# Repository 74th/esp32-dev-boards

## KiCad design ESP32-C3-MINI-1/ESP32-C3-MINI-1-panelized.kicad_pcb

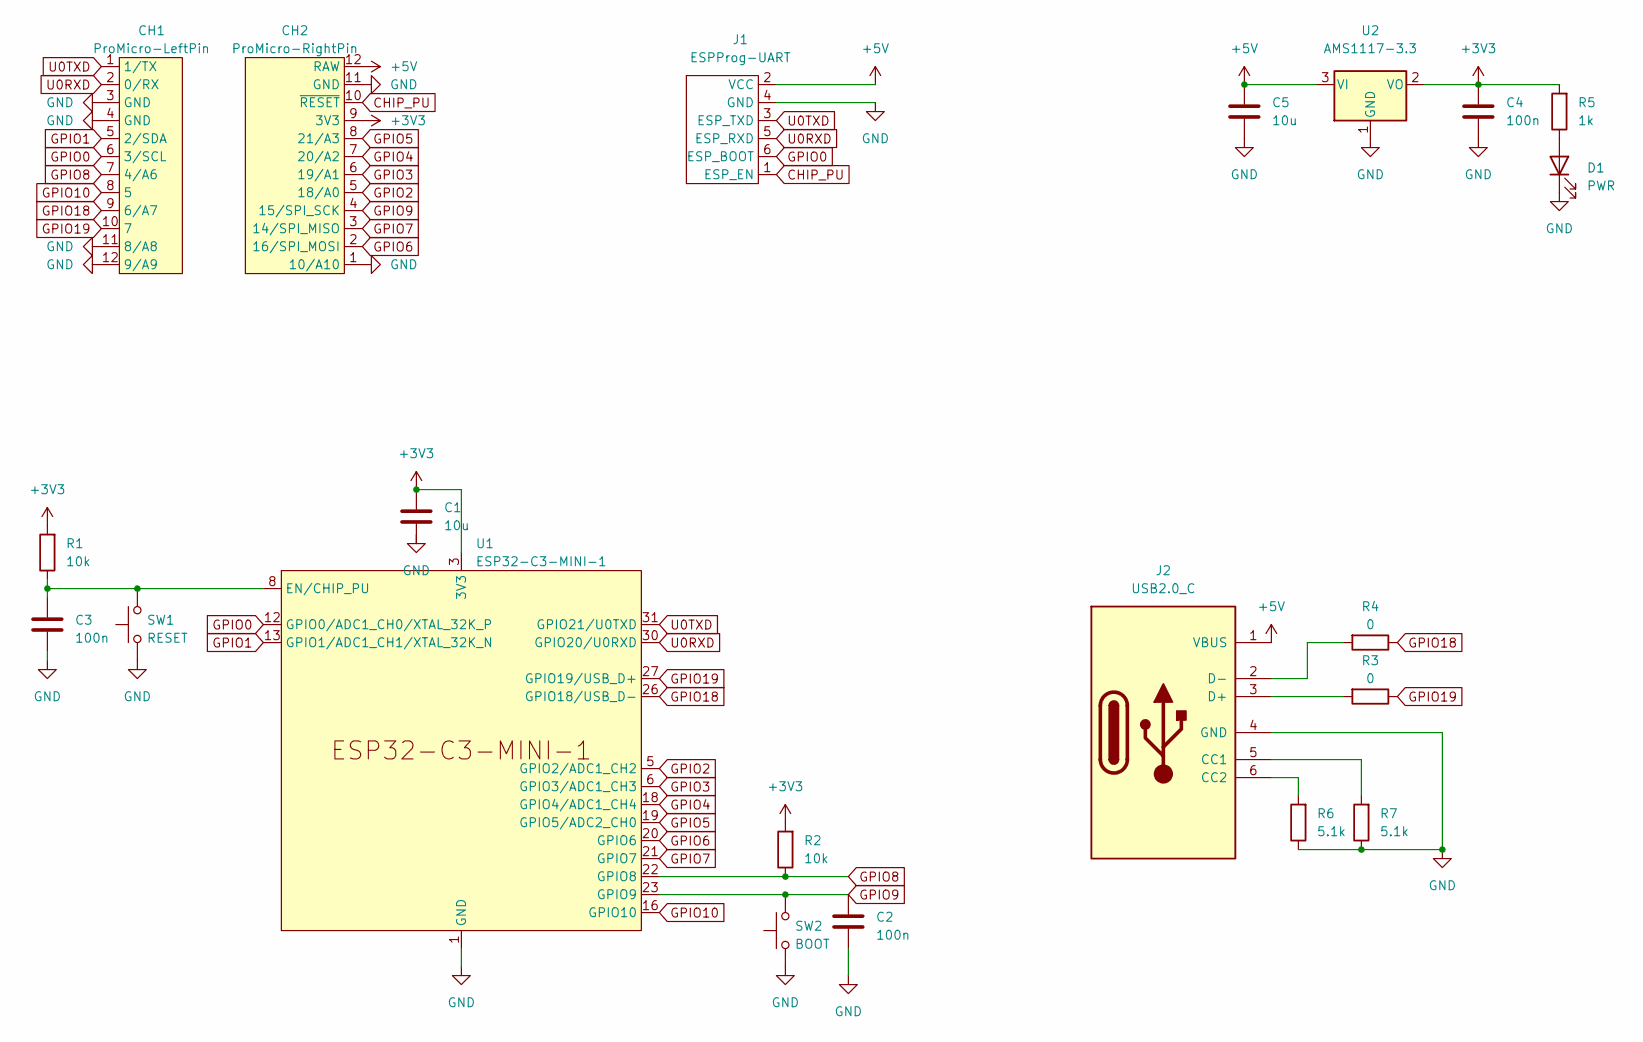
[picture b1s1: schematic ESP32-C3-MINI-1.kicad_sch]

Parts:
C1, C5: 10u; Capacitor_0805_2012
C2, C3, C4: 100n; Capacitor_0805_2012
CH1: ProMicro-LeftPin; ProMicro_LIKE_LEFT
CH2: ProMicro-RightPin; ProMicro_LIKE_RIGHT
D1: PWR; LED_0805_2012Metric_Pad1.15x1.40mm_HandSolder
J1: ESPProg-UART; BoxPinHeader_2x03_P1.27mm_Vertical
J2: USB2.0_C; USB-C-12-Pin-SMD
R1, R2: 10k; Register_0805_2012
R3, R4: 0; Register_0805_2012
R5: 1k; Register_0805_2012
R6, R7: 5.1k; Register_0805_2012
SW1: RESET; SKRPABE010
SW2: BOOT; SKRPABE010
U1: ESP32-C3-MINI-1
U2: AMS1117-3.3; Regulator_AMS1117_SOT-89

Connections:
+3V3: C1.1, C4.1, CH2.9 (3V3), R1.2, R2.2, R5.2, U1.3 (3V3), U2.2 (VO)
+5V: C5.1, CH2.12 (RAW), J1.2 (VCC), J2.1 (VBUS), U2.3 (VI)
CHIP_PU: CH2.10 (~RESET), J1.1 (ESP_EN)
GND: C2.2, C3.2, C4.2, C5.2, CH1.3 (GND), CH1.4 (GND), CH1.11 (8/A8), CH1.12 (9/A9), CH2.1 (10/A10), CH2.11 (GND), D1.1 (K), J1.4 (GND), J2.4 (GND), R6.1, R7.1, SW1.1, SW2.1, U1.1 (GND), U1.2 (GND), U1.11 (GND), U1.14 (GND), U1.36 (GND), U1.37 (GND), U1.38 (GND), U1.39 (GND), U1.40 (GND), U1.41 (GND), U1.42 (GND), U1.43 (GND), U1.44 (GND), U1.45 (GND), U1.46 (GND), U1.47 (GND), U1.48 (GND), U1.49 (GND), U1.50 (GND), U1.51 (GND), U1.52 (GND), U1.53 (GND), U2.1 (GND)
GPIO0: CH1.6 (3/SCL), J1.6 (ESP_BOOT), U1.12 (GPIO0/ADC1_CH0/XTAL_32K_P)
GPIO1: CH1.5 (2/SDA), U1.13 (GPIO1/ADC1_CH1/XTAL_32K_N)
GPIO2: CH2.5 (18/A0), U1.5 (GPIO2/ADC1_CH2)
GPIO3: CH2.6 (19/A1), U1.6 (GPIO3/ADC1_CH3)
GPIO4: CH2.7 (20/A2), U1.18 (GPIO4/ADC1_CH4)
GPIO5: CH2.8 (21/A3), U1.19 (GPIO5/ADC2_CH0)
GPIO6: CH2.2 (16/SPI_MOSI), U1.20 (GPIO6)
GPIO7: CH2.3 (14/SPI_MISO), U1.21 (GPIO7)
GPIO8: CH1.7 (4/A6), R2.1, U1.22 (GPIO8)
GPIO9: C2.1, CH2.4 (15/SPI_SCK), SW2.2, U1.23 (GPIO9)
GPIO10: CH1.8 (5), U1.16 (GPIO10)
GPIO18: CH1.9 (6/A7), R4.1, U1.26 (GPIO18/USB_D-)
GPIO19: CH1.10 (7), R3.1, U1.27 (GPIO19/USB_D+)
unnamed: D1.2 (A), R5.1
unnamed: J2.5 (CC1), R7.2
unnamed: J2.6 (CC2), R6.2
unnamed: J2.3 (D+), R3.2
unnamed: J2.2 (D-), R4.2
unnamed: C3.1, R1.1, SW1.2, U1.8 (EN/CHIP_PU)
U0RXD: CH1.2 (0/RX), J1.5 (ESP_RXD), U1.30 (GPIO20/U0RXD)
U0TXD: CH1.1 (1/TX), J1.3 (ESP_TXD), U1.31 (GPIO21/U0TXD)

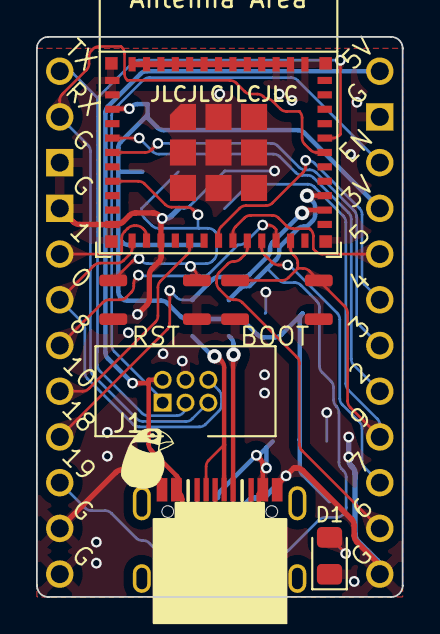
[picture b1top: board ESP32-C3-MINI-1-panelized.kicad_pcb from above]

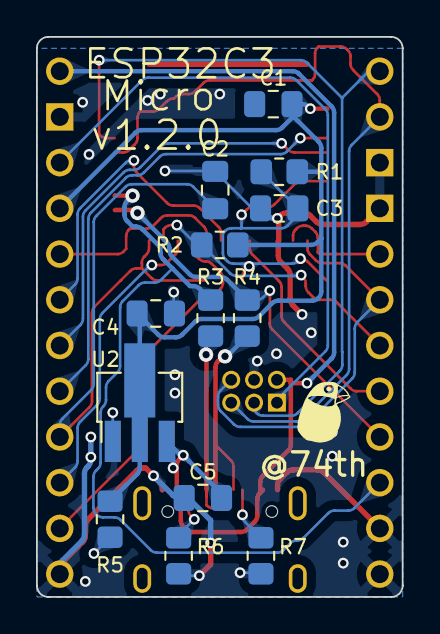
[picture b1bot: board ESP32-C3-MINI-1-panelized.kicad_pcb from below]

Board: 2 copper layers, 20.3 x 31.1 mm, 21 parts (13 on the bottom side), 25 nets.

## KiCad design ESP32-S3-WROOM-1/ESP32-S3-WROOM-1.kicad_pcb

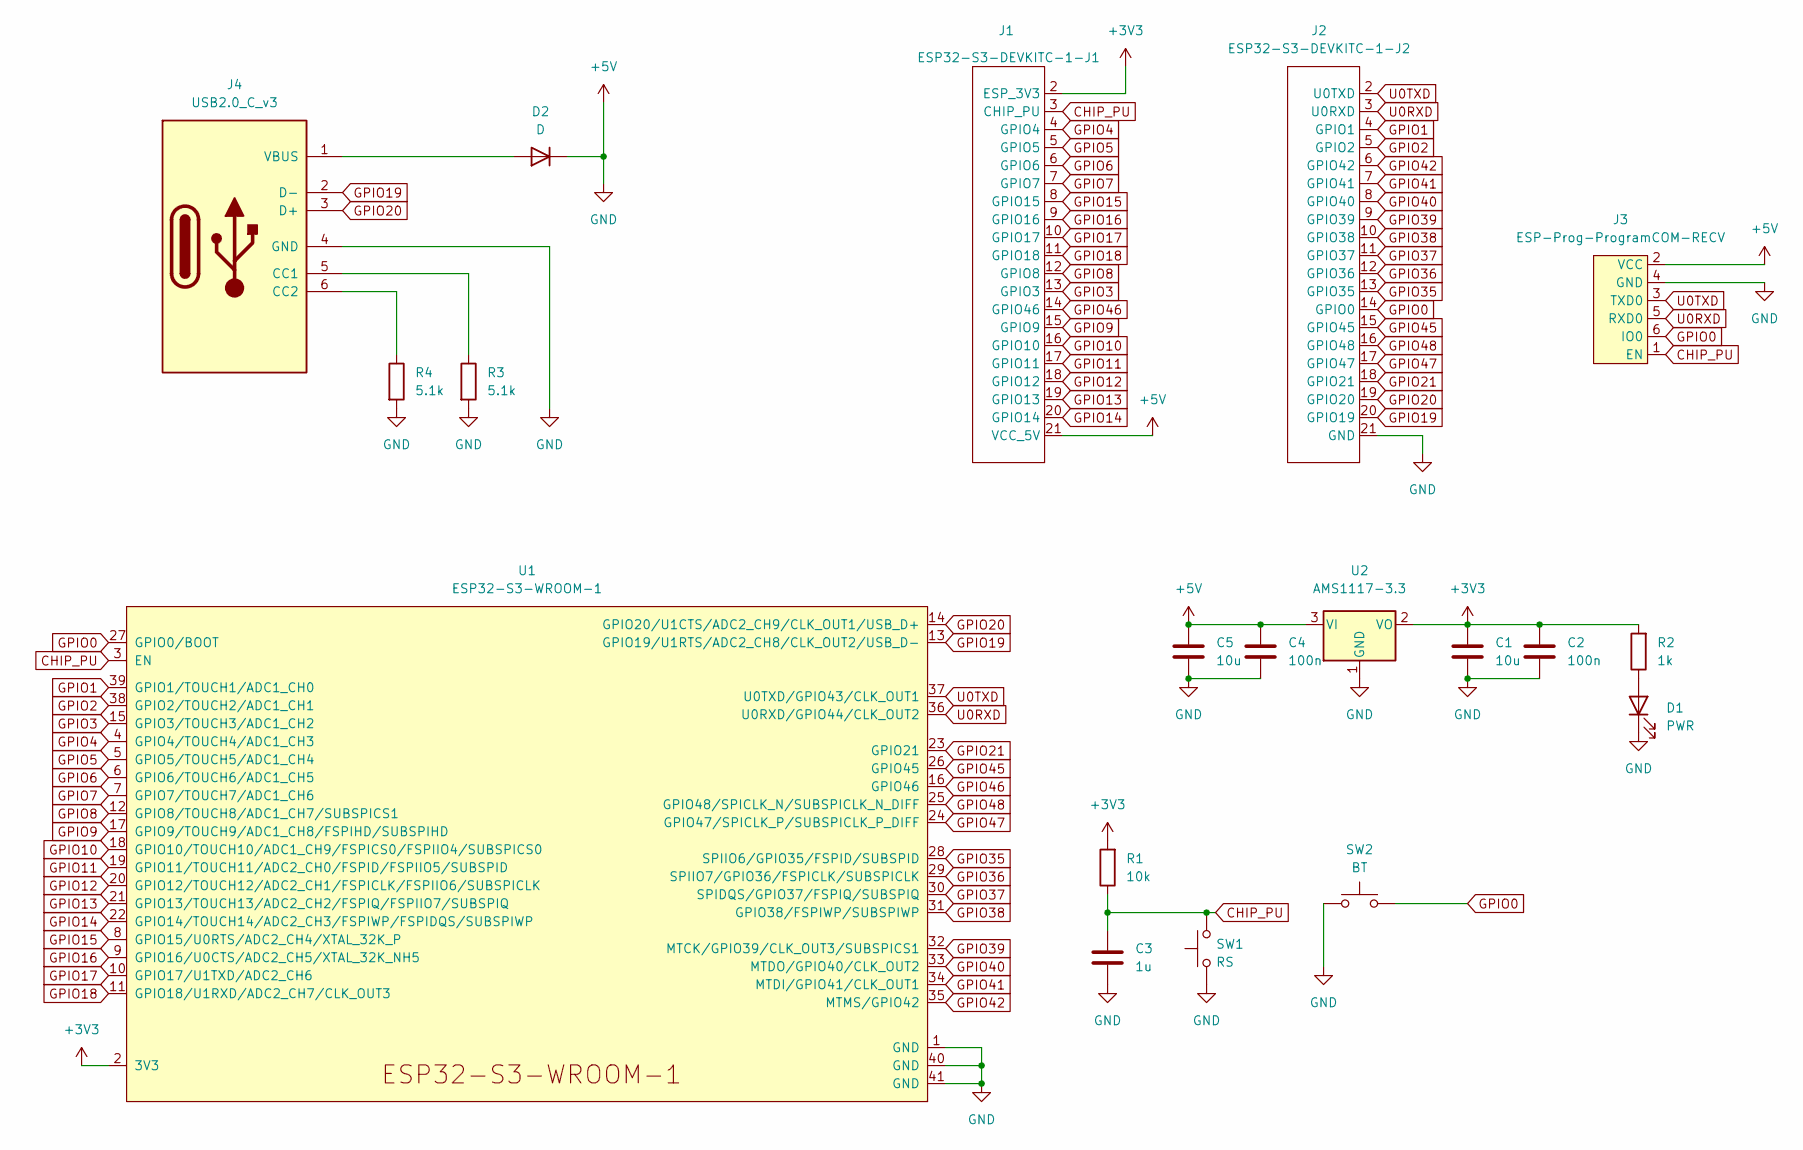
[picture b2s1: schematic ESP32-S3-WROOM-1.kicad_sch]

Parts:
C1, C5: 10u; Capacitor_0805_2012
C2, C4: 100n; Capacitor_0805_2012
C3: 1u; Capacitor_0805_2012
D1: PWR; LED_0805_2012Metric_Pad1.15x1.40mm_HandSolder
D2: D; D_SMA
J1: ESP32-S3-DEVKITC-1-J1; ESP32-S3-DEVKITC-J1-mini
J2: ESP32-S3-DEVKITC-1-J2; ESP32-S3-DEVKITC-J2-mini
J3: ESP-Prog-ProgramCOM-RECV; BoxPinHeader_2x03_P1.27mm_Vertical
J4: USB2.0_C_v3; USB-C-12-Pin-SMD
R1: 10k; Register_0805_2012
R2: 1k; Register_0805_2012
R3, R4: 5.1k; Register_0805_2012
SW1: RS; SKRPABE010
SW2: BT; SKRPABE010
U1: ESP32-S3-WROOM-1
U2: AMS1117-3.3; SOT-223-3_TabPin2

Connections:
+3V3: C1.1, C2.1, J1.2 (ESP_3V3), R1.2, R2.2, U1.2 (3V3), U2.2 (VO)
CHIP_PU: C3.1, J1.3 (CHIP_PU), J3.1 (EN), R1.1, SW1.2, U1.3 (EN)
GPIO0: J2.14 (GPIO0), J3.6 (IO0), SW2.2, U1.27 (GPIO0/BOOT)
GPIO1: J2.4 (GPIO1), U1.39 (GPIO1/TOUCH1/ADC1_CH0)
GPIO2: J2.5 (GPIO2), U1.38 (GPIO2/TOUCH2/ADC1_CH1)
GPIO3: J1.13 (GPIO3), U1.15 (GPIO3/TOUCH3/ADC1_CH2)
GPIO4: J1.4 (GPIO4), U1.4 (GPIO4/TOUCH4/ADC1_CH3)
GPIO5: J1.5 (GPIO5), U1.5 (GPIO5/TOUCH5/ADC1_CH4)
GPIO6: J1.6 (GPIO6), U1.6 (GPIO6/TOUCH6/ADC1_CH5)
GPIO7: J1.7 (GPIO7), U1.7 (GPIO7/TOUCH7/ADC1_CH6)
GPIO8: J1.12 (GPIO8), U1.12 (GPIO8/TOUCH8/ADC1_CH7/SUBSPICS1)
GPIO9: J1.15 (GPIO9), U1.17 (GPIO9/TOUCH9/ADC1_CH8/FSPIHD/SUBSPIHD)
GPIO10: J1.16 (GPIO10), U1.18 (GPIO10/TOUCH10/ADC1_CH9/FSPICS0/FSPIIO4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)
GPIO11: J1.17 (GPIO11), U1.19 (GPIO11/TOUCH11/ADC2_CH0/FSPID/FSPIIO5/S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)
GPIO12: J1.18 (GPIO12), U1.20 (GPIO12/TOUCH12/ADC2_CH1/FSPICLK/FSPIIO6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)
GPIO13: J1.19 (GPIO13), U1.21 (GPIO13/TOUCH13/ADC2_CH2/FSPIQ/FSPIIO7/S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)
GPIO14: J1.20 (GPIO14), U1.22 (GPIO14/TOUCH14/ADC2_CH3/FSPIWP/FSPIDQS/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)
GPIO15: J1.8 (GPIO15), U1.8 (GPIO15/U0RTS/ADC2_CH4/XTAL_32K_P)
GPIO16: J1.9 (GPIO16), U1.9 (GPIO16/U0CTS/ADC2_CH5/XTAL_32K_NH5)
GPIO17: J1.10 (GPIO17), U1.10 (GPIO17/U1TXD/ADC2_CH6)
GPIO18: J1.11 (GPIO18), U1.11 (GPIO18/U1RXD/ADC2_CH7/CLK_OUT3)
GPIO19: J2.20 (GPIO19), J4.2 (D-), U1.13 (GPIO19/U1RTS/ADC2_CH8/CLK_OUT2/USB_D-)
GPIO20: J2.19 (GPIO20), J4.3 (D+), U1.14 (GPIO20/U1CTS/ADC2_CH9/CLK_OUT1/USB_D+)
GPIO21: J2.18 (GPIO21), U1.23 (GPIO21)
GPIO35: J2.13 (GPIO35), U1.28 (SPIIO6/GPIO35/FSPID/SUBSPID)
GPIO36: J2.12 (GPIO36), U1.29 (SPIIO7/GPIO36/FSPICLK/SUBSPICLK)
GPIO37: J2.11 (GPIO37), U1.30 (SPIDQS/GPIO37/FSPIQ/SUBSPIQ)
GPIO38: J2.10 (GPIO38), U1.31 (GPIO38/FSPIWP/SUBSPIWP)
GPIO39: J2.9 (GPIO39), U1.32 (MTCK/GPIO39/CLK_OUT3/SUBSPICS1)
GPIO40: J2.8 (GPIO40), U1.33 (MTDO/GPIO40/CLK_OUT2)
GPIO41: J2.7 (GPIO41), U1.34 (MTDI/GPIO41/CLK_OUT1)
GPIO42: J2.6 (GPIO42), U1.35 (MTMS/GPIO42)
GPIO45: J2.15 (GPIO45), U1.26 (GPIO45)
GPIO46: J1.14 (GPIO46), U1.16 (GPIO46)
GPIO47: J2.17 (GPIO47), U1.24 (GPIO47/SPICLK_P/SUBSPICLK_P_DIFF)
GPIO48: J2.16 (GPIO48), U1.25 (GPIO48/SPICLK_N/SUBSPICLK_N_DIFF)
unnamed: D1.2 (A), R2.1
unnamed: D2.2 (A), J4.1 (VBUS)
unnamed: J4.5 (CC1), R3.1
unnamed: J4.6 (CC2), R4.1
U0RXD: J2.3 (U0RXD), J3.5 (RXD0), U1.36 (U0RXD/GPIO44/CLK_OUT2)
U0TXD: J2.2 (U0TXD), J3.3 (TXD0), U1.37 (U0TXD/GPIO43/CLK_OUT1)

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
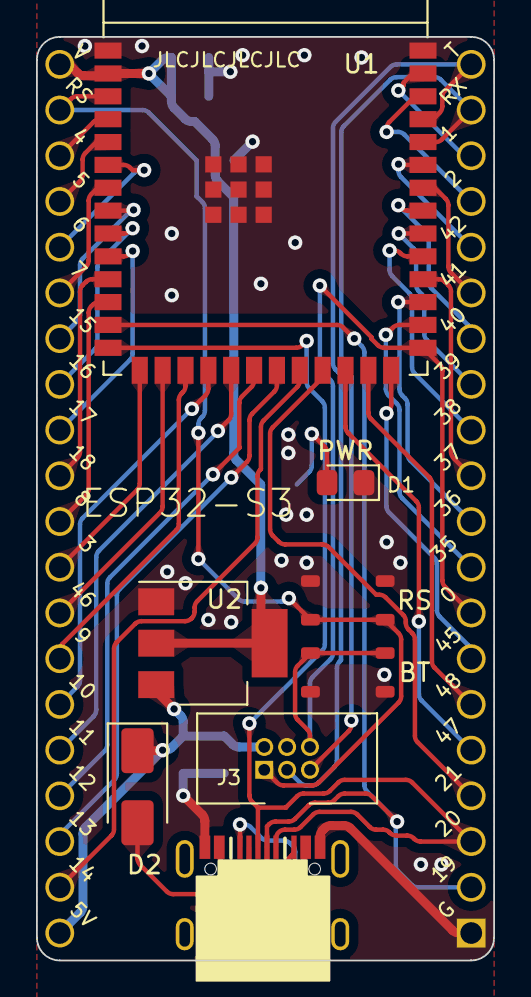
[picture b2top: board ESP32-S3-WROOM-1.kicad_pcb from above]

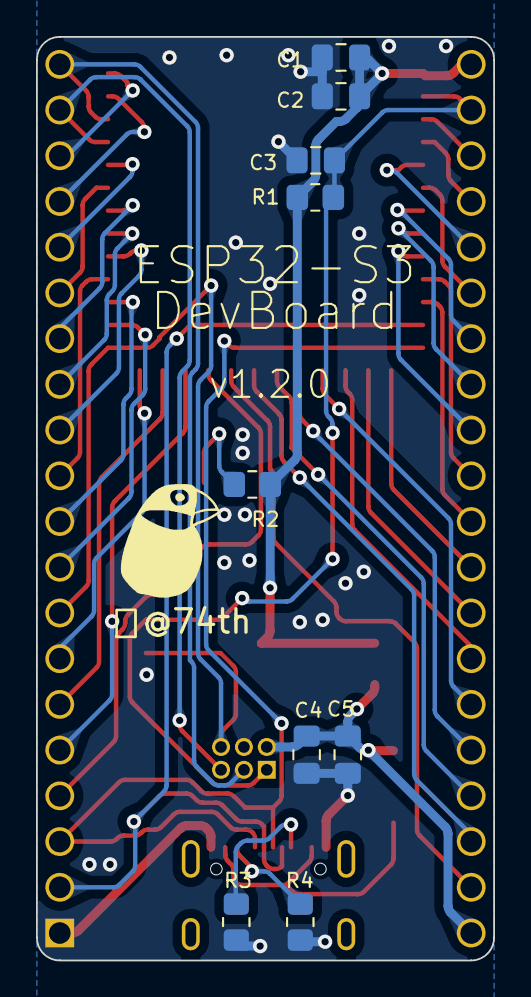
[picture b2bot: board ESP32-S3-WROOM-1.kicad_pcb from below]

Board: 2 copper layers, 25.4 x 51.3 mm, 19 parts (9 on the bottom side), 44 nets.

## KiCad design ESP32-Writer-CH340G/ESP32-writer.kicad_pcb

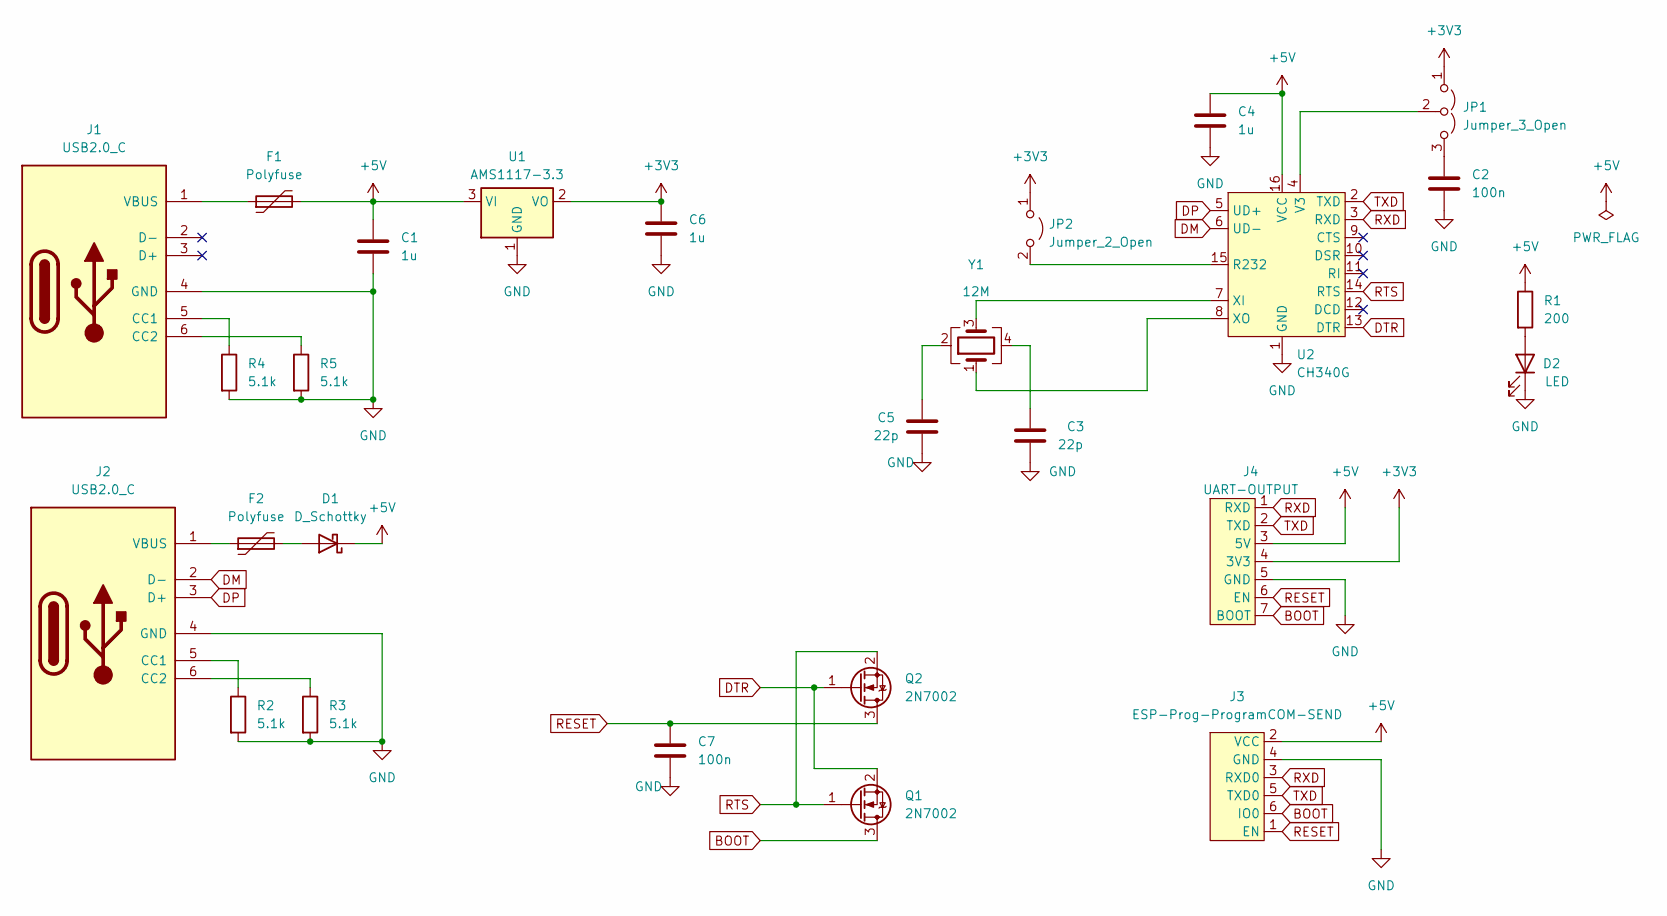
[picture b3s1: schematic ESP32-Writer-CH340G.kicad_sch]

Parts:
C1, C4, C6: 1u; Capacitor_0805_2012
C2, C7: 100n; Capacitor_0805_2012
C3, C5: 22p; Capacitor_0805_2012
D1: D_Schottky; D_SMA
D2: LED; LED_0805_2012Metric_Pad1.15x1.40mm_HandSolder
F1, F2: Polyfuse; ResettableFuse_KT6-1100SMDI
J1, J2: USB2.0_C; USB-C-12-Pin-MidMount-ali-v5
J3: ESP-Prog-ProgramCOM-SEND; BoxPinHeader_2x03_P1.27mm_Vertical
J4: UART-OUTPUT; UART
JP1: Jumper_3_Open; SolderJumper-3_P1.3mm_Open_RoundedPad1.0x1.5mm_NumberLabels
JP2: Jumper_2_Open; SolderJumper-2_P1.3mm_Open_RoundedPad1.0x1.5mm
Q1, Q2: 2N7002; SOT-23
R1: 200; Register_0805_2012
R2, R3, R4, R5: 5.1k; Register_0805_2012
U1: AMS1117-3.3; SOT-223-3_TabPin2
U2: CH340G; SOP-16_3.9x9.9mm_P1.27mm
Y1: 12M; Crystal_SMD_3225-4Pin_3.2x2.5mm_HandSoldering

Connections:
+3V3: C6.1, J4.4 (3V3), JP1.1 (A), JP2.1 (A), U1.2 (VO)
+5V: C1.1, C4.1, D1.1 (K), F1.2, J3.2 (VCC), J4.3 (5V), R1.1, U1.3 (VI), U2.16 (VCC)
BOOT: J3.6 (IO0), J4.7 (BOOT), Q1.3 (D)
DM: J2.2 (D-), U2.6 (UD-)
DP: J2.3 (D+), U2.5 (UD+)
DTR: Q1.2 (S), Q2.1 (G), U2.13 (DTR)
GND: C1.2, C2.2, C3.1, C4.2, C5.1, C6.2, C7.2, D2.1 (K), J1.4 (GND), J2.4 (GND), J3.4 (GND), J4.5 (GND), R2.2, R3.2, R4.2, R5.2, U1.1 (GND), U2.1 (GND)
unnamed: C5.2, Y1.2
unnamed: C3.2, Y1.4
unnamed: D1.2 (A), F2.2
unnamed: D2.2 (A), R1.2
unnamed: J1.5 (CC1), R4.1
unnamed: J1.6 (CC2), R5.1
unnamed: F1.1, J1.1 (VBUS)
unnamed: J2.5 (CC1), R2.1
unnamed: J2.6 (CC2), R3.1
unnamed: F2.1, J2.1 (VBUS)
unnamed: C2.1, JP1.3 (B)
unnamed: JP1.2 (C), U2.4 (V3)
unnamed: JP2.2 (B), U2.15 (R232)
unnamed: U2.7 (XI), Y1.3
unnamed: U2.8 (XO), Y1.1
RESET: C7.1, J3.1 (EN), J4.6 (EN), Q2.3 (D)
RTS: Q1.1 (G), Q2.2 (S), U2.14 (RTS)
RXD: J3.3 (RXD0), J4.1 (RXD), U2.3 (RXD)
TXD: J3.5 (TXD0), J4.2 (TXD), U2.2 (TXD)

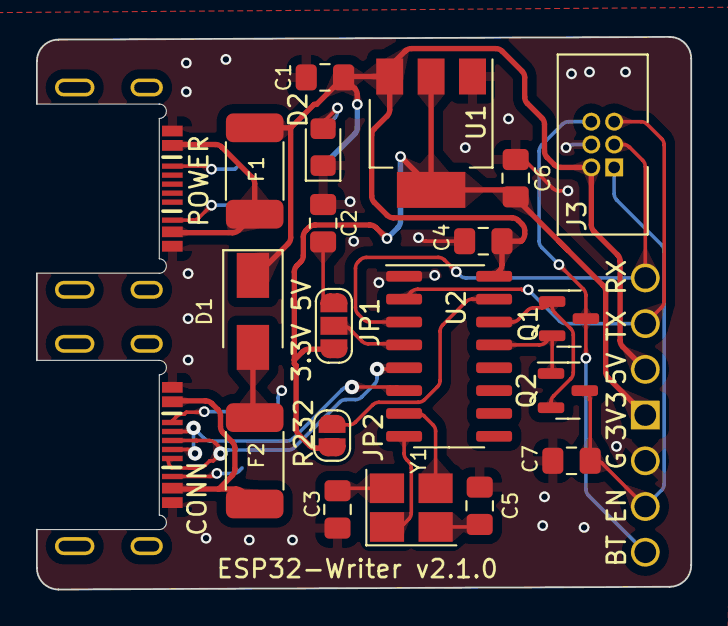
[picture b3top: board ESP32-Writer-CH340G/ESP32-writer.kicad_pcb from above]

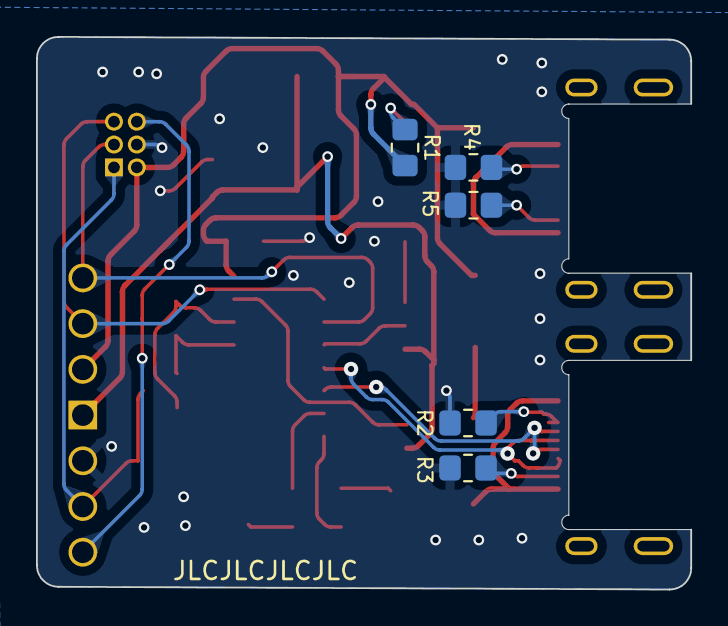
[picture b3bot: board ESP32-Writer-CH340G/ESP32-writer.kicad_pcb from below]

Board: 2 copper layers, 36.4 x 30.7 mm, 27 parts (5 on the bottom side), 26 nets.

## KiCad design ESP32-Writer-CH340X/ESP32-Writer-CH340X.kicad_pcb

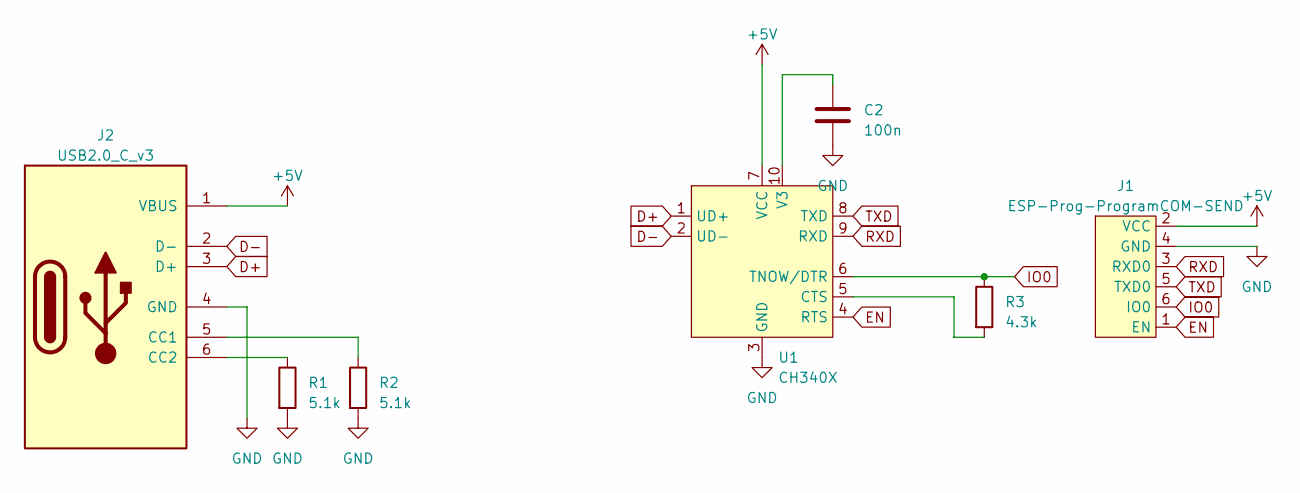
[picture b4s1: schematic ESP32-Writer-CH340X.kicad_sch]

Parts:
C2: 100n; Capacitor_0603_1608
J1: ESP-Prog-ProgramCOM-SEND; BoxPinHeader_2x03_P1.27mm_Vertical
J2: USB2.0_C_v3; USB-C-12-Pin-SMD
R1, R2: 5.1k; Register_0603_1608
R3: 4.3k; Register_0603_1608
U1: CH340X; MSOP-10_3x3mm_P0.5mm

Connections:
+5V: J1.2 (VCC), J2.1 (VBUS), U1.7 (VCC)
D+: J2.3 (D+), U1.1 (UD+)
D-: J2.2 (D-), U1.2 (UD-)
EN: J1.1 (EN), U1.4 (RTS)
GND: C2.2, J1.4 (GND), J2.4 (GND), R1.2, R2.2, U1.3 (GND)
IO0: J1.6 (IO0), R3.1, U1.6 (TNOW/DTR)
unnamed: J2.5 (CC1), R2.1
unnamed: J2.6 (CC2), R1.1
unnamed: R3.2, U1.5 (CTS)
unnamed: C2.1, U1.10 (V3)
RXD: J1.3 (RXD0), U1.9 (RXD)
TXD: J1.5 (TXD0), U1.8 (TXD)

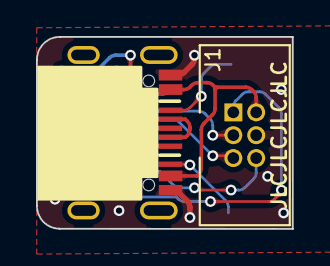
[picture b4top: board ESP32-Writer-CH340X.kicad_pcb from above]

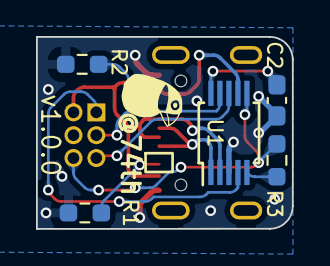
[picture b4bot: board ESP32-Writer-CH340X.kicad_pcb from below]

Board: 2 copper layers, 14.2 x 10.7 mm, 7 parts (5 on the bottom side), 12 nets.

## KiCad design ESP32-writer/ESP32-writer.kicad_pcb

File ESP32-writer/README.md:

# CH340C 使用 ESP-Prog 互換 USB シリアル

ESP32 Writer として使える USB シリアル変換です。

- ESP32 の EN、GPIO0 用のピンを持ち、esptools を使ったアップロードで、EN、GPIO0 を自動で操作します。
- ESP32 のデバッグツールである ESP-Prog に付属する USB シリアル互換の、ボックスピンヘッダを持ちます。
- 電源用 USB と通信用 USB が別れています。これにより、電力の小さい PC の USB でも追加の電源用 USB で電源供給できます。

## なぜ ESP-Prog ではなくこれを作ったのか

- USB を、電源用と通信用の 2 つをもたせたいから。これがないと USB の給電能力が低い場合、PC で Write 後に、電源供給 USB への繋ぎ変えが必要になり面倒くさい。

## なぜ市販の USB シリアル変換アダプタではなくこれを作ったのか

- EN、BOOT を操作する必要がないようにしたいから。

## v2.0.1 ~ 2.0.2

### 部品表

| ID  | 指定子      | 名称                                      | 数量 |
| --- | ----------- | ----------------------------------------- | ---- |
| 1   | C1,C4       | 0805 キャパシタ 10u                       | 2    |
| 2   | J1,J3       | USB 2.0 Type-C ソケット                   | 2    |
| 3   | R4,R1,R2,R5 | 0805 レジスタ 5.1k                        | 4    |
| 4   | Q2,Q1       | MOSFET SN7002                             | 2    |
| 5   | C2,C3       | 0805 キャパシタ 100n                      | 2    |
| 6   | D1          | 0805 LED                                  | 1    |
| 7   | D2          | ショットキーダイオード 340mV@1A PMEG2010ER       | 1    |
| 8   | U2          | ESP-Prog 互換 1.27 ボックスピンヘッダ 2x3 | 1    |
| 9   | U1          | USB シリアル IC CH340C                    | 1    |
| 10  | J2          | UART ピンヘッダ                           | 1    |
| 11  | R3          | 0805 レジスタ 1k                          | 1    |

- ダイオードの電圧低下が大きい場合、ダイオードの代わりに 0R レジスタを入れることもできます（製作者はそれで使っています）

[部品の調達先はこちらを確認下さい ../parts.md](../parts.md)

### ドキュメント

- [Semantics v2.0.1 = 2.0.2](ESP32-writer-2.0.1-semantics.pdf)
- [PCB v2.0.1](ESP32-writer-2.0.1-pcb.pdf)

## 変更履歴

- v2.1.0
  - CH340G に変更（ESP-Writer-CH340G として、別プロダクトへ変更）
- v2.0.2
  - USB Type-C ソケットのフットプリントを実装しやすいものに変更
- v2.0.1
  - 配線ミスを修正
- v2.0.0
  - ESP-Prog 互換 Box Pin Header を追加

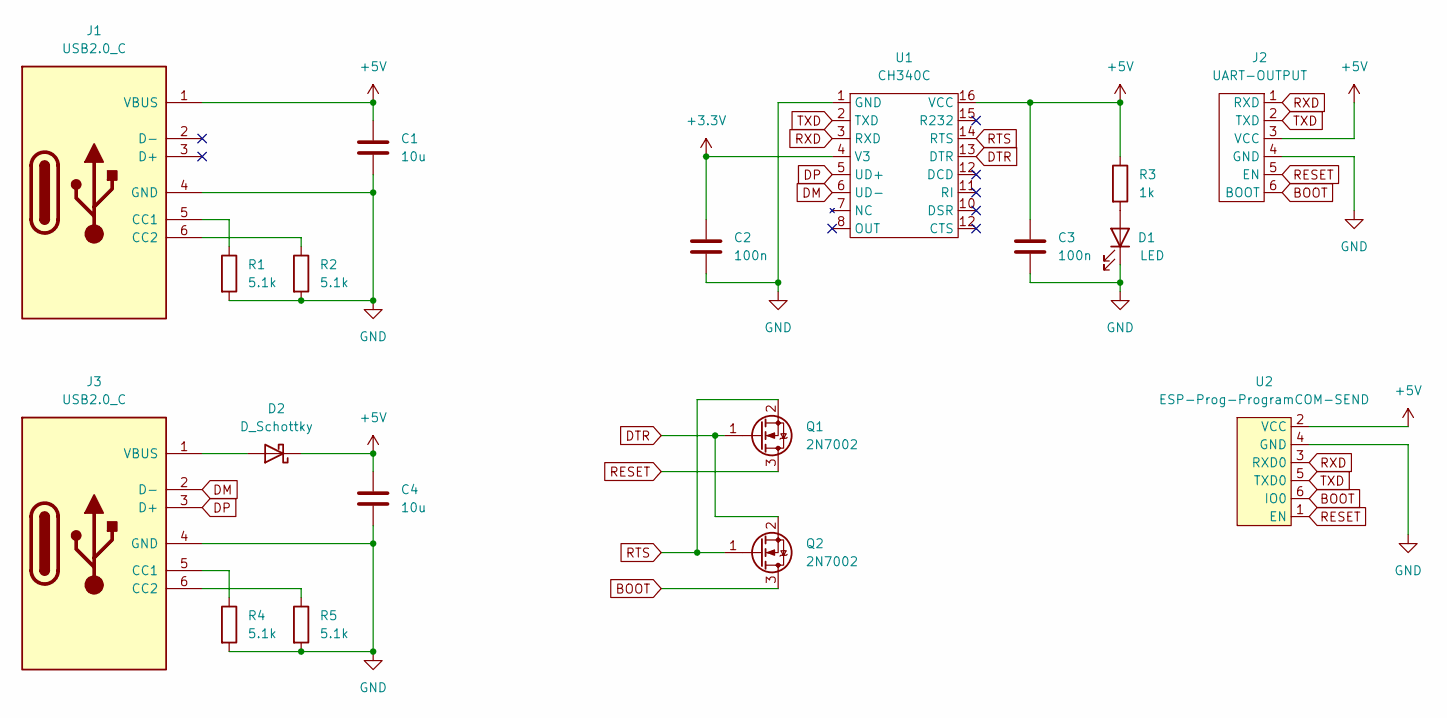
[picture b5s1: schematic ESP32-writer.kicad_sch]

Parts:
C1, C4: 10u; Capacitor_0805_2012
C2, C3: 100n; Capacitor_0805_2012
D1: LED; LED_0805_2012Metric_Pad1.15x1.40mm_HandSolder
D2: D_Schottky; D_SMA
J1, J3: USB2.0_C; USB-C-12-Pin-MidMount-ali-v5
J2: UART-OUTPUT; UART
Q1, Q2: 2N7002; SOT-23
R1, R2, R4, R5: 5.1k; Register_0805_2012
R3: 1k; Register_0805_2012
U1: CH340C; SOP-16_3.9x9.9mm_P1.27mm
U2: ESP-Prog-ProgramCOM-SEND; BoxPinHeader_2x03_P1.27mm_Vertical

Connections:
+3.3V: C2.1, U1.4 (V3)
+5V: C1.1, C3.1, C4.1, D2.1 (K), J1.1 (VBUS), J2.3 (VCC), R3.1, U1.16 (VCC), U2.2 (VCC)
BOOT: J2.6 (BOOT), Q2.3 (D), U2.6 (IO0)
DM: J3.2 (D-), U1.6 (UD-)
DP: J3.3 (D+), U1.5 (UD+)
DTR: Q1.1 (G), Q2.2 (S), U1.13 (DTR)
GND: C1.2, C2.2, C3.2, C4.2, D1.1 (K), J1.4 (GND), J2.4 (GND), J3.4 (GND), R1.2, R2.2, R4.2, R5.2, U1.1 (GND), U2.4 (GND)
unnamed: D1.2 (A), R3.2
unnamed: D2.2 (A), J3.1 (VBUS)
unnamed: J1.5 (CC1), R1.1
unnamed: J1.6 (CC2), R2.1
unnamed: J3.5 (CC1), R4.1
unnamed: J3.6 (CC2), R5.1
RESET: J2.5 (EN), Q1.3 (D), U2.1 (EN)
RTS: Q1.2 (S), Q2.1 (G), U1.14 (RTS)
RXD: J2.1 (RXD), U1.3 (RXD), U2.3 (RXD0)
TXD: J2.2 (TXD), U1.2 (TXD), U2.5 (TXD0)

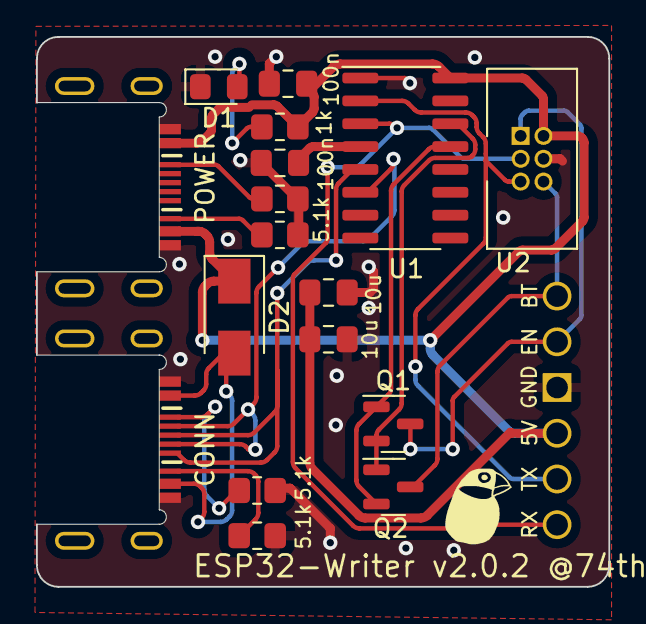
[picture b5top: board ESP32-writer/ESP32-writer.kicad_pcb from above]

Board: 2 copper layers, 31.8 x 30.6 mm, 18 parts (0 on the bottom side), 17 nets.
